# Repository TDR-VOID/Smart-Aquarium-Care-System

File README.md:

# Smart Aquarium Care System

## Overview

This innovative device is designed to autonomously manage aquarium upkeep, eliminating the need for constant human intervention. It ensures precise fish feeding based on predetermined quantities and intervals set by the owner, while also checking the precise temperature for the fish using the DHT11 temperature sensor. Additionally, users will be notified of low food levels and out-of-range temperatures via SMS messages. Atmega32 microcontroller, LCD Display, DHT11 Temperature Sensor, Servo Motor, and GSM 800L module were used to develop this device. 

The LCD display shows elapsed time since the last feeding cycle, enabling the owner to manually feed the fish if necessary, adjusting based on the displayed time. Moreover, it includes alerts for unfavourable temperature ranges and notifies users when food supplies are low, enhancing fish care and ensuring a conducive environment for aquatic life.

Developed with the support of repaired components and external resources, this system promotes hassle-free aquarium maintenance, catering to both the fish's well-being and the owner's convenience.

## Features
- **Automated Feeding:** The system autonomously manages feeding cycles based on predefined schedules and quantities, eliminating the need for constant human intervention.
- **Customizable Feeding Schedules:** Owners can easily set specific feeding times and quantities for their fish, providing tailored care.
- **LCD Display for Monitoring:** Displays elapsed time since the last feeding cycle, allowing owners to manually feed if necessary and adjust schedules based on displayed information.
- **Temperature Monitoring and Alerts:** Incorporates a DHT11 Temperature Sensor to monitor water temperature, alerting users about unfavourable temperature ranges that could harm aquatic life.
- **Low Food Supply Notification:** Notifies the user when food supplies are running low, ensuring continuous care for the fish and preventing interruptions in feeding cycles.
- **Enhanced Fish Care:** Promotes hassle-free aquarium maintenance, catering to the well-being of the fish by providing consistent feeding and a conducive environment.

## Components Used

- Atmega32 Microcontroller
- SIM800L GSM Module
- DHT11 Temperature Sensor
- Servo Motor
- 16x2 LED display
  
<br />

## License

[MIT License](LICENSE)

<br />

> [!NOTE]
> All operational information for the device is detailed in the **User Manual** & **Project Report** PDF documents.

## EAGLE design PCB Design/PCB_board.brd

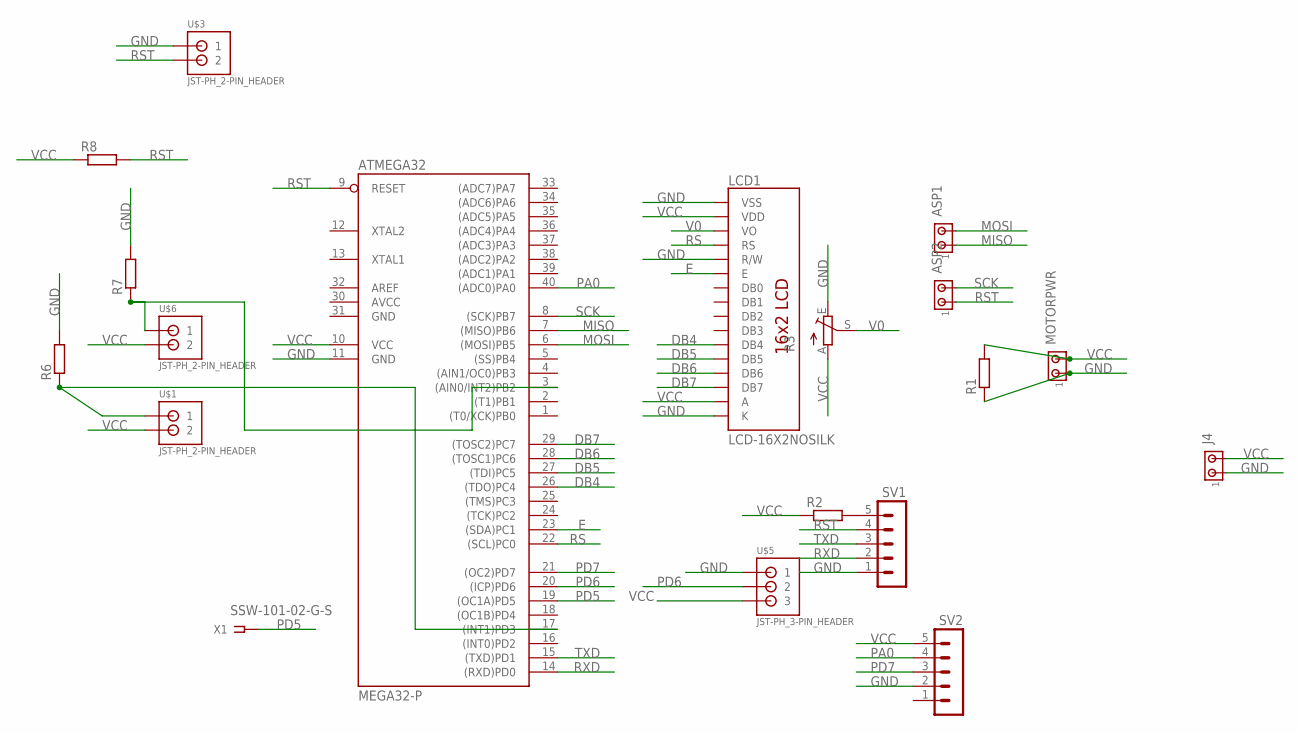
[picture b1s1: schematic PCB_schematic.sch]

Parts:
ASP1, ASP2: MTA02-100; 10X02MTA
ATMEGA32: MEGA32-P; DIL40
J4: MTA02-100; 10X02MTA
LCD1: LCD-16X2NOSILK; LCD-16X2_NOSILK
MOTORPWR: MTA02-100; 10X02MTA
R1, R2, R6, R7, R8: R-EU_0204/7; 0204/7
R3: TRIM_EU-CA6V; CA6V
SV1, SV2: MA05-1
U$1, U$3, U$6: JST-PH_2-PIN_HEADER; JST_B2B-PH_HEADER
U$5: JST-PH_3-PIN_HEADER; JST_B3B-PH_HEADER
X1: SSW-101-02-G-S

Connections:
AVCC: ATMEGA32.30 (AVCC)
DB4: ATMEGA32.26 ((TDO)PC4), LCD1.11 (DB4)
DB5: ATMEGA32.27 ((TDI)PC5), LCD1.12 (DB5)
DB6: ATMEGA32.28 ((TOSC1)PC6), LCD1.13 (DB6)
DB7: ATMEGA32.29 ((TOSC2)PC7), LCD1.14 (DB7)
E: ATMEGA32.23 ((SDA)PC1), LCD1.6 (E)
GND: ATMEGA32.11 (GND), ATMEGA32.31 (GND), J4.1, LCD1.1 (VSS), LCD1.5 (R/W), LCD1.16 (K), MOTORPWR.1, R1.1, R3.E, R6.2, R7.2, SV1.1, SV2.2, U$3.P1 (1), U$5.P1 (1)
MISO: ASP1.1, ATMEGA32.7 ((MISO)PB6)
MOSI: ASP1.2, ATMEGA32.6 ((MOSI)PB5)
unnamed: R2.2, SV1.5
unnamed: ATMEGA32.3 ((AIN0/INT2)PB2), R7.1, U$6.P1 (1)
unnamed: ATMEGA32.17 ((INT1)PD3), R6.1, U$1.P1 (1)
PA0: ATMEGA32.40 ((ADC0)PA0), SV2.4
PD5: ATMEGA32.19 ((OC1A)PD5), X1.1
PD6: ATMEGA32.20 ((ICP)PD6), U$5.P2 (2)
PD7: ATMEGA32.21 ((OC2)PD7), SV2.3
RS: ATMEGA32.22 ((SCL)PC0), LCD1.4 (RS)
RST: ASP2.1, ATMEGA32.9 (RESET), R8.2, SV1.4, U$3.P2 (2)
RXD: ATMEGA32.14 ((RXD)PD0), SV1.2
SCK: ASP2.2, ATMEGA32.8 ((SCK)PB7)
TXD: ATMEGA32.15 ((TXD)PD1), SV1.3
V0: LCD1.3 (VO), R3.S
VCC: ATMEGA32.10 (VCC), J4.2, LCD1.2 (VDD), LCD1.15 (A), MOTORPWR.2, R1.2, R2.1, R3.A, R8.1, SV2.5, U$1.P2 (2), U$5.P3 (3), U$6.P2 (2)

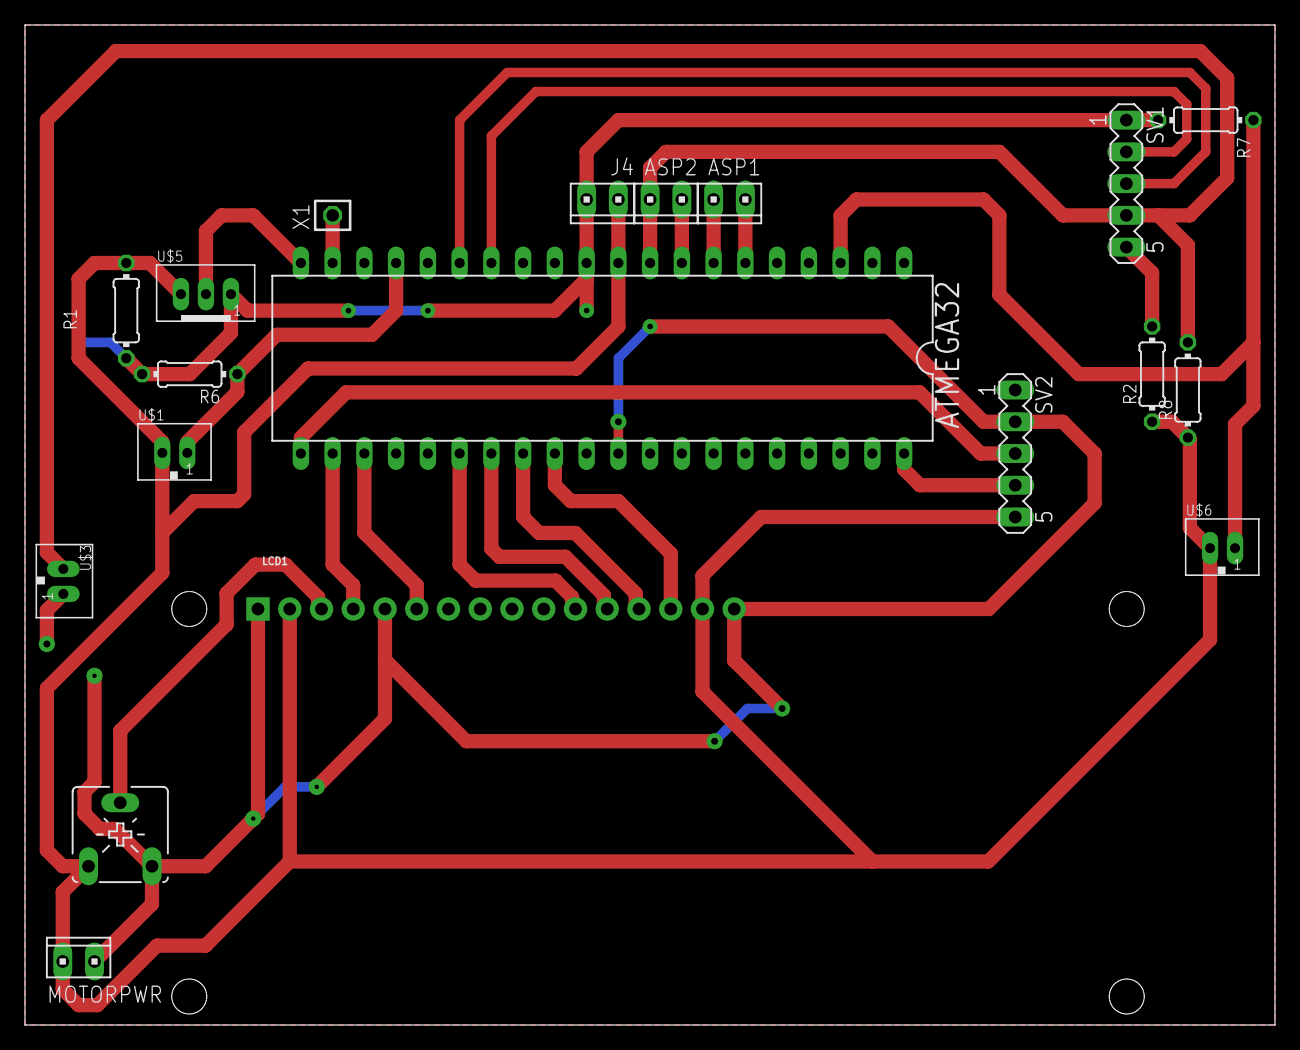
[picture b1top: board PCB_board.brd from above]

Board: 2 copper layers, 100.0 x 80.0 mm, 19 parts (0 on the bottom side), 22 nets.

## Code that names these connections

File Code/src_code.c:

#define F_CPU 8000000UL			/* # Define CPU Frequency (CPU clock frequency for the AVR microcontroller)*/
#define BAUD_PRESCALE (((F_CPU / (USART_BAUDRATE * 16UL))) - 1) /* GSM_USART_BAUDRATE: This is the desired baud rate for UART communication */
#include <string.h> 			/* # Include the standard C string library for string manipulation (strlen)*/
#include <avr/io.h>				/* # Include the AVR I/O (Input/Output) header file for accessing hardware registers. */
#include <util/delay.h>			/* # Include delay header file  (_dealy_ms)*/
#include <avr/interrupt.h>		/* #Include the AVR interrupt header file for enabling and managing interrupts.*/


/* 
   Smart Aquarium Care System Project
   LCD initialization and functions adapted from "ElectronicWings"
   https://www.electronicwings.com/avr-atmega/interfacing-lcd-16x2-in-4-bit-mode-with-atmega-16-32-
*/

#define LCD_Dir  DDRC			/* Define LCD data port data direction registry */
#define LCD_Port PORTC			/* Define LCD data port */
#define RS PC0					/* Define Register Select pin */
#define EN PC1 					/* Define Enable signal pin */


volatile unsigned int e =1, q=0, k=0; /* e - Variable assign for 'Gate Openings' , */
volatile unsigned int l=0,s=0,m=0,h=0; /*l - create the ms, s - seconds, m - minutes, h - hours*/
volatile _Bool active=1; /*For the first screen of the LCD*/
volatile unsigned char u=4;
int i = 0;


/* Declare a character variable int_str1,int_str2,int_str3,int_str4 */
char int_str1; 
char int_str2;
char int_str3;
char int_str4;




// Function prototypes
void UART_init(long USART_BAUDRATE);
unsigned char UART_RxChar(void);
void UART_TxChar(char ch);
void UART_SendString(char *str);
void LCD_Clear();
void LCD_Command( unsigned char cmnd );
void LCD_Char( unsigned char data );
void LCD_Init (void);
void LCD_String (char *str);
void initTimer2CTC(void);
void LCD_String_xy (char row, char pos, char *str);
void externalInt(void);
void ServoTime();




void LCD_Command( unsigned char cmnd )
{
	LCD_Port = (LCD_Port & 0x0F) | (cmnd & 0xF0); /* sending upper nibble */
	LCD_Port &= ~ (1<<RS);		/* RS=0, command reg. */
	LCD_Port |= (1<<EN);		/* Enable pulse */
	_delay_us(1);
	LCD_Port &= ~ (1<<EN);

	_delay_us(200);

	LCD_Port = (LCD_Port & 0x0F) | (cmnd << 4);  /* sending lower nibble */
	LCD_Port |= (1<<EN);
	_delay_us(1);
	LCD_Port &= ~ (1<<EN);
	_delay_ms(2);
}

void LCD_Char( unsigned char data )
{
	LCD_Port = (LCD_Port & 0x0F) | (data & 0xF0); /* sending upper nibble */
	LCD_Port |= (1<<RS);		/* RS=1, data reg. */
	LCD_Port|= (1<<EN);
	_delay_us(1);
	LCD_Port &= ~ (1<<EN);

	_delay_us(200);

	LCD_Port = (LCD_Port & 0x0F) | (data << 4); /* sending lower nibble */
	LCD_Port |= (1<<EN);
	_delay_us(1);
	LCD_Port &= ~ (1<<EN);
	_delay_ms(2);
}

void LCD_Init (void)			/* LCD Initialize function */
{
	LCD_Dir = 0xFF;			/* Make LCD port direction as o/p */
	_delay_ms(20);			/* LCD Power ON delay always >15ms */
	LCD_Command(0x02);		/* send for 4 bit initialization of LCD  */
	LCD_Command(0x28);              /* 2 line, 5*7 matrix in 4-bit mode */
	LCD_Command(0x0c);              /* Display on cursor off*/
	LCD_Command(0x06);              /* Increment cursor (shift cursor to right)*/
	LCD_Command(0x01);              /* Clear display screen*/
	_delay_ms(2);
}

void LCD_String (char *str)		/* Send string to LCD function */
{
	int i;
	for(i=0;str[i]!=0;i++)		/* Send each char of string till the NULL */
	{
		LCD_Char (str[i]);
	}
}

void LCD_String_xy (char row, char pos, char *str)	/* Send string to LCD with xy position */
{
	if (row == 0 && pos<16)
	LCD_Command((pos & 0x0F)|0x80);	/* Command of first row and required position<16 */
	else if (row == 1 && pos<16)
	LCD_Command((pos & 0x0F)|0xC0);	/* Command of first row and required position<16 */
	LCD_String(str);/* Call LCD string function */
}

void LCD_Clear()
{
	LCD_Command (0x01);		/* Clear display */
	_delay_ms(2);
	LCD_Command (0x80);		/* Cursor at home position */
}

void externalInt(void){
    DDRD = DDRD & ~(1<<PD3); /*Setting up DDRD PIN3 as input (set 0 wihtout changing other pins)*/
    DDRB = DDRB & ~(1<<PB2); /*Setting up DDRB PIN2 as input*/
    GICR |= (1<<INT1) | (1<<INT2); /*enable external interrupt 1 & 0 ; INT1 = PD3 , INT2 = PB2 (General Interrupt
Control Register)*/
    MCUCR |= (1<<ISC10) | (1<<ISC11);  /*The rising edge of INT1 generates an interrupt request.*/
    MCUCSR |= (1<<ISC2); /*falling edge on
INT2 activates the interrupt*/
}
 
 
void initTimer2CTC(void){   //CTC mode; Clock ps/8; OC0 disconnected
    TCCR2 = 0X00; /*sets the Timer/Counter Control Register 2 (TCCR2) to zero*/
    TCCR2 |= 1<<CS22|1<<WGM21; /*CS22-clkT2S/64 (From prescaler) , CTC Mode - Clear Timer on Compare Match */
    TIMSK |= 1<<OCIE2;   /*Output Compare Match Interrupt for Timer 2*/
    OCR2=124; /* Output Compare Register 2  to 124*/
	/*DesiredTime = F_CPU / (Prescale * (OCR2 + 1))*/
} 



void ServoTime()
{
	//int i;
	for(i=0;i<5;i++)
	{
		_delay_ms(200);

	}

}


/*Initialize UART with the specified baud rate*/ 
void UART_init(long USART_BAUDRATE){
    UCSRB |= (1 << RXEN) | (1 << TXEN); 	/*Enabling RXEN allows the UART to receive data, and enabling TXEN allows it to transmit data (Turn on transmission and reception)*/
    UCSRC |= (1 << URSEL) | (1 << UCSZ0) | (1 << UCSZ1); // Use 8-bit character sizes
    UBRRL = BAUD_PRESCALE; 			// Load lower 8-bits of the baud rate value
    UBRRH = (BAUD_PRESCALE >> 8); 		// Load upper 8-bits
}

// Receive a character from UART
unsigned char UART_RxChar(void){		
    while ((UCSRA & (1 << RXC)) == 0); 		// Wait till data is received
    return(UDR); 				// Return the received byte
}

// Transmit a character through UART
void UART_TxChar(char ch){
    while (!(UCSRA & (1<<UDRE))); 		// Wait for empty transmit buffer
    UDR = ch;
}

// Send a string through UART
void UART_SendString(char *str){
    unsigned char j=0;
    while (str[j] != 0){ 			// Send string till null terminator
        UART_TxChar(str[j]);
        j++;
        
    
        
    }
}


int main()
{	
	sei(); /*enable global interrupts in an AVR */
	
	externalInt();

	LCD_Init();
	LCD_Clear();
	LCD_String_xy(0,4,"Welcome");
	_delay_ms(2000);
	
	
	//Configure TIMER1
	TCCR1A|=(1<<COM1A1)|(1<<COM1B1)|(1<<WGM11);		 	//NON Inverted PWM
	TCCR1B|=(1<<WGM13)|(1<<WGM12)|(1<<CS11)|(1<<CS10);	//PRESCALER=64 MODE 14(FAST PWM)
	ICR1=4999;	//fPWM=50Hz (Period = 20ms Standard).
	DDRD|=(1<<PD4)|(1<<PD5);	//PWM Pins as Out


	char int_str1[20]; /* Declare an array to store a string of up to 20 characters*/
	char int_str2[20];
	char int_str3[20];
	char int_str4[20];

	while(active){
	sprintf(int_str4, "%02d", u);
	LCD_String_xy(0,0,"Feeding Interval :");	/* Initialization ofLCD*/
	LCD_Command(0xC0);
	LCD_String_xy(1,7,int_str4);		/* Go to 2nd line*/
	_delay_ms(10);

	
	}
	
	initTimer2CTC();
	
	_delay_ms(100);

	while(1){
	
	if (k==6){
	UART_init(9600);		// Initialize UART communication with a baud rate of 9600
        UART_SendString("AT\r\n");	// Send AT command to the GSM module
        _delay_ms(200);
        UART_SendString("ATE0\r\n");	// Disable command echo
        _delay_ms(200);
        UART_SendString("AT+CMGF=1\r\n");	// Set SMS text mode
        _delay_ms(200);
        UART_SendString("AT+CMGS=\"xxxxxxxxx\"\r\n");	// Set recipient phone number
        _delay_ms(200);
        UART_SendString("Food Level Low");// Send SMS text
        UART_TxChar(26);		// Send Ctrl+Z to indicate end of SMS
    	k=0;
  
	
	}
	
	if(s==u){
	for(int n=0;n<e;n++){
	k=k+1;
	
	OCR1A=175;
	ServoTime();

	OCR1A=220;
	ServoTime();
	s=0;

	}
	}
	

	sprintf(int_str1, "%02d", e); /*%d give only one digit*/
	sprintf(int_str2, "%02d", s);
	sprintf(int_str3, "%02d", m);
	
	
	LCD_String_xy(0,0,"Gate Openings:");/* Initialization ofLCD*/
	LCD_String_xy(0,14,int_str1);	/* Write string on 1st line of LCD*/
	LCD_Command(0xC0);
	LCD_String_xy(1,0,"Time: ");		/* Go to 2nd line*/
	LCD_String_xy(1,7,int_str3);
	LCD_String_xy(1,9,":");
	LCD_String_xy(1,10,int_str2);	/* Write string on 2nd line*/
	_delay_ms(10);

	
	}	
	
		
	
}


ISR(TIMER2_COMP_vect ){ 
	l=l+1;
		if(l == 1000){
			s+=1 ;
			l=0;
			if(s==60){
				m=m+1;
				s=0;
				if (m==60){
					h=h+1;
					m=0;
					}
				}
				 
		}
		
	}




ISR(INT1_vect){
   
   if(active){
	   u+=2;
	   if(u>13){
		u=4;
   }
   
   }
   else if(active==0){ e=e+1;
    if(e==9){
    e=0;
    }
       
}
}
ISR(INT2_vect){
  
  if(active){
	active=0;
  
 
  
  }
  if(active==0){
  
   TIMSK ^= 1<<OCIE2; /*TIMSK (Timer/Counter Interrupt Mask Register)*/
}

}
    

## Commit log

2023-12-22 Add files via upload
    This User Guide provides step-by-step instructions and detailed information on setting up, configuring, and using the Smart Aquarium Care System
2023-12-22 Create PCB_board
2024-03-19 Create td
2024-03-19 Create 1
2024-08-31 Create LICENSE

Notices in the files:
parts and their libraries:
SparkFun-Displays: Licensing: Creative Commons ShareAlike 4.0 International - https://creativecommons.org/licenses/by-sa/4.0
